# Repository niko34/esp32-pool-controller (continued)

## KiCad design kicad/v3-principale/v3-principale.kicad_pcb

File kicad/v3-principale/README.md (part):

# Carte principale du PCB v3 — composants et connexions

Troisième carte du v3 ([feature-215](../../specs/features/todo/feature-215-conception-du-pcb-v3.md)),
à côté de la carte de mesure ([`../v3-mesure-std/`](../v3-mesure-std/README.md)).
Elle porte l'ESP32, le port USB, l'horloge et sa pile, les sorties de puissance, les
régulateurs et la sonde de température.

⏳ **État au 2026-11-25 : liste des composants et tableau des connexions, version 0.2 —
relus une fois par `electronics-reviewer`, quatre erreurs corrigées (voir « Relecture »).
Schéma rév. 0.2 écrit par script, relu par `electronics-reviewer` : aucune erreur, deux remarques portées.
**Carte rév. 0.1 placée et routée le 2026-11-26** — contrôle des règles : 0 violation, 0 liaison
manquante, 0 écart avec le schéma. Relue par `electronics-reviewer` : aucune erreur, cinq
retouches portées. ⏳ Rien n'est encore ouvert dans KiCad par l'utilisateur.** Horloge : **DS3231SN** depuis le 2026-11-26 (décision de l'utilisateur : la qualité l'emporte sur le nombre de fabricants et sur le prix) ; carte retouchée à la main, contrôle des règles identique.

🆕 **Rév. 0.3 du 2026-11-28 — étude des parasites et de la fiabilité** (demande de l'utilisateur).
Trois changements, détaillés plus bas : une **coupure commune du 12 V des pompes avec relecture de
leurs sorties**, la **protection du bornier de la sonde de température**, et le cuivre mal relié
(piste au bord retirée, plans de masse cousus). Les règles à tenir désormais, avec leurs raisons,
sont dans [`../REGLES-CEM-ET-FIABILITE.md`](../REGLES-CEM-ET-FIABILITE.md) ;
`python3 scripts/verifier_regles_cartes.py v3-principale` les contrôle.
⚠️ **Deux broches de l'ESP32 changent de rôle par rapport au v2** : voir le tableau des connexions.

## Les fichiers de ce dossier

| Fichier | Rôle |
|---|---|
| `generer_schema.py` | écrit le schéma depuis les connexions ci-dessous. ⚠️ Le relancer **réécrit** le schéma en entier. Il lit les symboles standard de KiCad (paquet `kicad-symbols`) |
| `v3-principale.kicad_sch` | le schéma, format A1, un cadre par fonction |
| `v3-principale.kicad_sym`, `sym-lib-table` | le symbole du module ESP32, absent des bibliothèques de KiCad |
| `v3-principale.kicad_pro` | le projet |

**Comment le schéma est fait** : chaque broche porte un bout de fil et une étiquette ; deux
broches sont reliées quand elles portent la même étiquette. Il n'y a pas de long fil à suivre.

**Vérifié le 2026-11-25** : la liste des connexions que KiCad extrait du schéma est identique
à celle voulue — 62 fils, 20 broches en l'air (schéma rév. 0.2).
**Rév. 0.3, vérifié le 2026-11-28** : 63 fils, 23 broches en l'air, 106 pièces ; le schéma du
projet est exactement celui que produit `generer_schema.py` (contrôle C2 du vérificateur).
⚠️ Toute pièce nouvelle s'ajoute dans la **dernière section** du script : il numérote les pièces
dans l'ordre où elles sont écrites.

**Le contrôle électrique de KiCad rend un message attendu** : « deux sorties d'alimentation
reliées », entre la broche V3 du pont USB et la sortie du régulateur 3,3 V. C'est le câblage
que demande le fabricant du pont quand il est alimenté en 3,3 V. Les autres messages
viennent des bibliothèques absentes de la machine qui a généré le schéma.

**Ce que le schéma ne contient pas encore**
- les empreintes du module ESP32 (absente de KiCad, à dessiner d'après la fiche d'Espressif)
  et du support de pile (celle posée est provisoire) ;
- les trous de fixation, qui viendront avec la carte.

Règle suivie : D8 de feature-215 — composants courants, posés par l'atelier, un équivalent
d'un autre fabricant sur la même empreinte, la qualité restant un critère majeur.

## Ce que la carte reprend du v2, et ce qui change

| Fonction | v2 | v3 |
|---|---|---|
| ESP32 | carte de développement enfichée | module soudé, mémoire PSRAM comprise |
| Programmation | par le port de la carte de développement | port USB-C sur la carte |
| Horloge | module externe enfiché (`J11`) | puce et pile sur la carte |
| Sorties 12 V (2 pompes, filtration, éclairage, auxiliaire) | 5 transistors TO-220 traversants | 5 transistors CMS |
| Entrée 12 V : fusible, anti-inversion, écrêteur | traversants | CMS, même principe |
| 3,3 V et 5 V | deux modules enfichés | régulateurs sur la carte — ⚠️ **provisoire, voir plus bas** |
| Température | une sonde sur la carte, une prise pour la sonde d'eau | inchangé |
| Mesure pH et ORP | sur la carte | partie sur la carte de mesure, reliée par câble |

⭐ **Les broches de l'ESP32 ne changent pas** (ADR-0012) : le même firmware pilote les
mêmes sorties sur le v2 et le v3.
⚠️ **Sauf pour doser, depuis la rév. 0.3** : les pompes ne reçoivent le 12 V que si le logiciel
met IO4 à 1 (voir « Sécurité des pompes »). Le firmware du v2, qui ne connaît pas cette broche,
pilote tout le reste mais ne fait tourner aucune pompe sur cette carte.

## Disposition dans le boîtier — décidée le 2026-11-25 (utilisateur)

Relevé sur le fichier d'assemblage FreeCAD du boîtier V14 (reçu le 2026-11-25, conservé hors
du dépôt). Origine : coin bas-gauche du boîtier vu de face, cotes en mm.

| Élément | Position relevée |
|---|---|
| Boîtier | 210 × 175, profondeur 94 (119,5 avec les pompes) |
| Alimentation RPS-30-12 | X 18,8 à 69,6 · Y 39,9 à 116,1 ; son capot va jusqu'à X = 75,6 et monte à 40 mm du fond |
| Carte v2 | X 76,6 à 196 · Y 13,5 à 132,9, dos à 12 mm du fond |
| Pompes doseuses (sur le capot avant) | moteurs Ø 25,5 centrés en (65 ; 91) et (145 ; 91), profonds de 44,9 mm : leur arrière est à 43 mm du fond, soit 10,5 mm au-dessus des composants |
| Entrées de câbles (paroi du bas) | trois, à X = 44 / 68 / 88, à **49 mm du fond** : les câbles arrivent au-dessus du capot de l'alimentation |
| Prises des sondes (paroi du bas) | X = 123,1 et 159,4, à 19,8 mm du fond |
| Plots de fixation murale | (25 ; 150) et (185 ; 150) : ils bornent la carte en haut |

**Organisation retenue (« option N »)** — le dessin général du boîtier ne change pas, il
gagne **20 mm en hauteur** (210 × 195) **et 10 mm en profondeur** (104 mm, 129,5 mm avec les
pompes) :

⚠️ **Profondeur portée à 114 mm le 2026-11-26** (139,5 mm avec les pompes), pour qu'un
transformateur de 48 mm tienne sous la pompe de gauche (feature-218). Le boîtier adapté est
`boitier/v15/` : ses cotes font foi.

- alimentation à gauche, pompes à leur place actuelle ;
- carte de mesure en bas à droite, prises des sondes sur les perçages existants ;
- **carte principale rectangulaire de 119 × 100 mm** au-dessus : X 77 à 196, Y 62 à 162 ;
- le connecteur de liaison est sur le bord du bas de la carte principale, **face à celui de
  la carte de mesure** ;
- **tout se branche par le dessus**, sur des borniers débrochables ;
- **tous les câbles du boîtier sont sur le bord gauche, en une seule colonne** (utilisateur,
  2026-11-26), de haut en bas : arrivée 12 V — en haut à gauche, pour la relier par le haut à
  l'alimentation —, filtration, éclairage, auxiliaire, sonde d'eau, détecteur de débit ;
- les deux pompes, dont les fils viennent du capot, sont sur le bord du haut ;
- le 5 V d'essai est à l'intérieur de la carte : aucun câble du boîtier n'y arrive ;
- ⛔ aucun connecteur haut sous le moteur de la pompe de droite : centre en (68 ; 71) sur la
  carte, Ø 25,5, 29 mm de libre au-dessus de la carte ;
- antenne de l'ESP32 dans le coin haut-droit.

**Connecteurs — décidé le 2026-11-25 (utilisateur) : uniquement des borniers débrochables**
pour tout ce qui reçoit des fils. On visse les fils sur une fiche, puis on l'enfiche par le
dessus : aucune place n'est nécessaire sur le côté.

| Connexion | Bornier |
|---|---|
| Arrivée 12 V, filtration, éclairage, auxiliaire, 5 V d'essai | 5,08 mm, 2 broches |
| Sonde de température de l'eau | 5,08 mm, 3 broches |
| Pompe pH, pompe chlore, détecteur de débit | 3,81 mm, 2 broches |

Restent d'un autre type : la liaison vers la carte de mesure (JST XH 8 voies, câble tout
fait), la prise USB-C et l'embase de débogage.

**Repérage par la couleur** (utilisateur, 2026-11-25) : les prises de même format sont
distinguées par une pastille ou un cerclage de couleur, sur la carte et sur la fiche.
L'idée de borniers à broches vides pour empêcher les erreurs a été écartée : fonctionnelle,
mais pas élégante.
⚠️ Risque assumé, à couvrir par les couleurs : le pas de 3,81 mm sépare les pompes des
sorties de filtration et d'éclairage, mais rien n'empêche mécaniquement d'inverser les deux
pompes, ni d'enficher le détecteur de débit sur une sortie de pompe (court-circuit du 12 V
à travers le transistor dès que la pompe est commandée). ⏳ À faire à la carte : sérigraphie
de couleur ou repère net à côté de chaque prise.

**Pourquoi 10 mm de profondeur en plus** (utilisateur, 2026-11-25) — jeux mesurés sur le
fichier d'assemblage, moteur de 44,9 mm de profondeur (cote « nominale », ⏳ à mesurer sur
une pompe réelle, cosses comprises) :

| Entre | Aujourd'hui | Avec 10 mm de plus |
|---|---|---|
| moteur de la pompe de gauche et capot de l'alimentation | 3,1 mm | 13,1 mm |
| moteur de la pompe de gauche et l'alimentation | 10,1 mm | 20,1 mm |
| moteur de la pompe de droite et la carte principale | 29,7 mm | 39,7 mm |

Le moteur de gauche empiétait aussi sur la zone réservée aux câbles devant la carte.

⏳ À faire avec le boîtier : déplacer les deux plots de fixation du haut, vérifier la
hauteur d'un bornier débrochable avec sa fiche (environ 20 mm), relever la référence des
fiches à vis (une par câble, à fournir avec l'appareil).

## La carte (2026-11-26)

119 × 100 mm, quatre couches, quatre trous M3. ⚠️ **Le coin haut-droit est découpé** sous
l'antenne du module ESP32 (x 97,5 à 119, y 0 à 6) : l'antenne dépasse dans le vide, comme le
demande Espressif. `generer_carte.py` pose encore un contour rectangulaire ; c'est la
retouche 6 qui le découpe. Couches : composants et signaux dessus, masse
continue en couche 2, 3,3 V en couche 3, signaux et masse dessous. Des plans de masse
entourent les pistes sur les deux faces extérieures.

| Fichier | Rôle |
|---|---|
| `generer_carte.py` | pose les composants, les trous et les deux plans internes. ⚠️ Le relancer **réécrit** la carte et **efface le routage** |
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
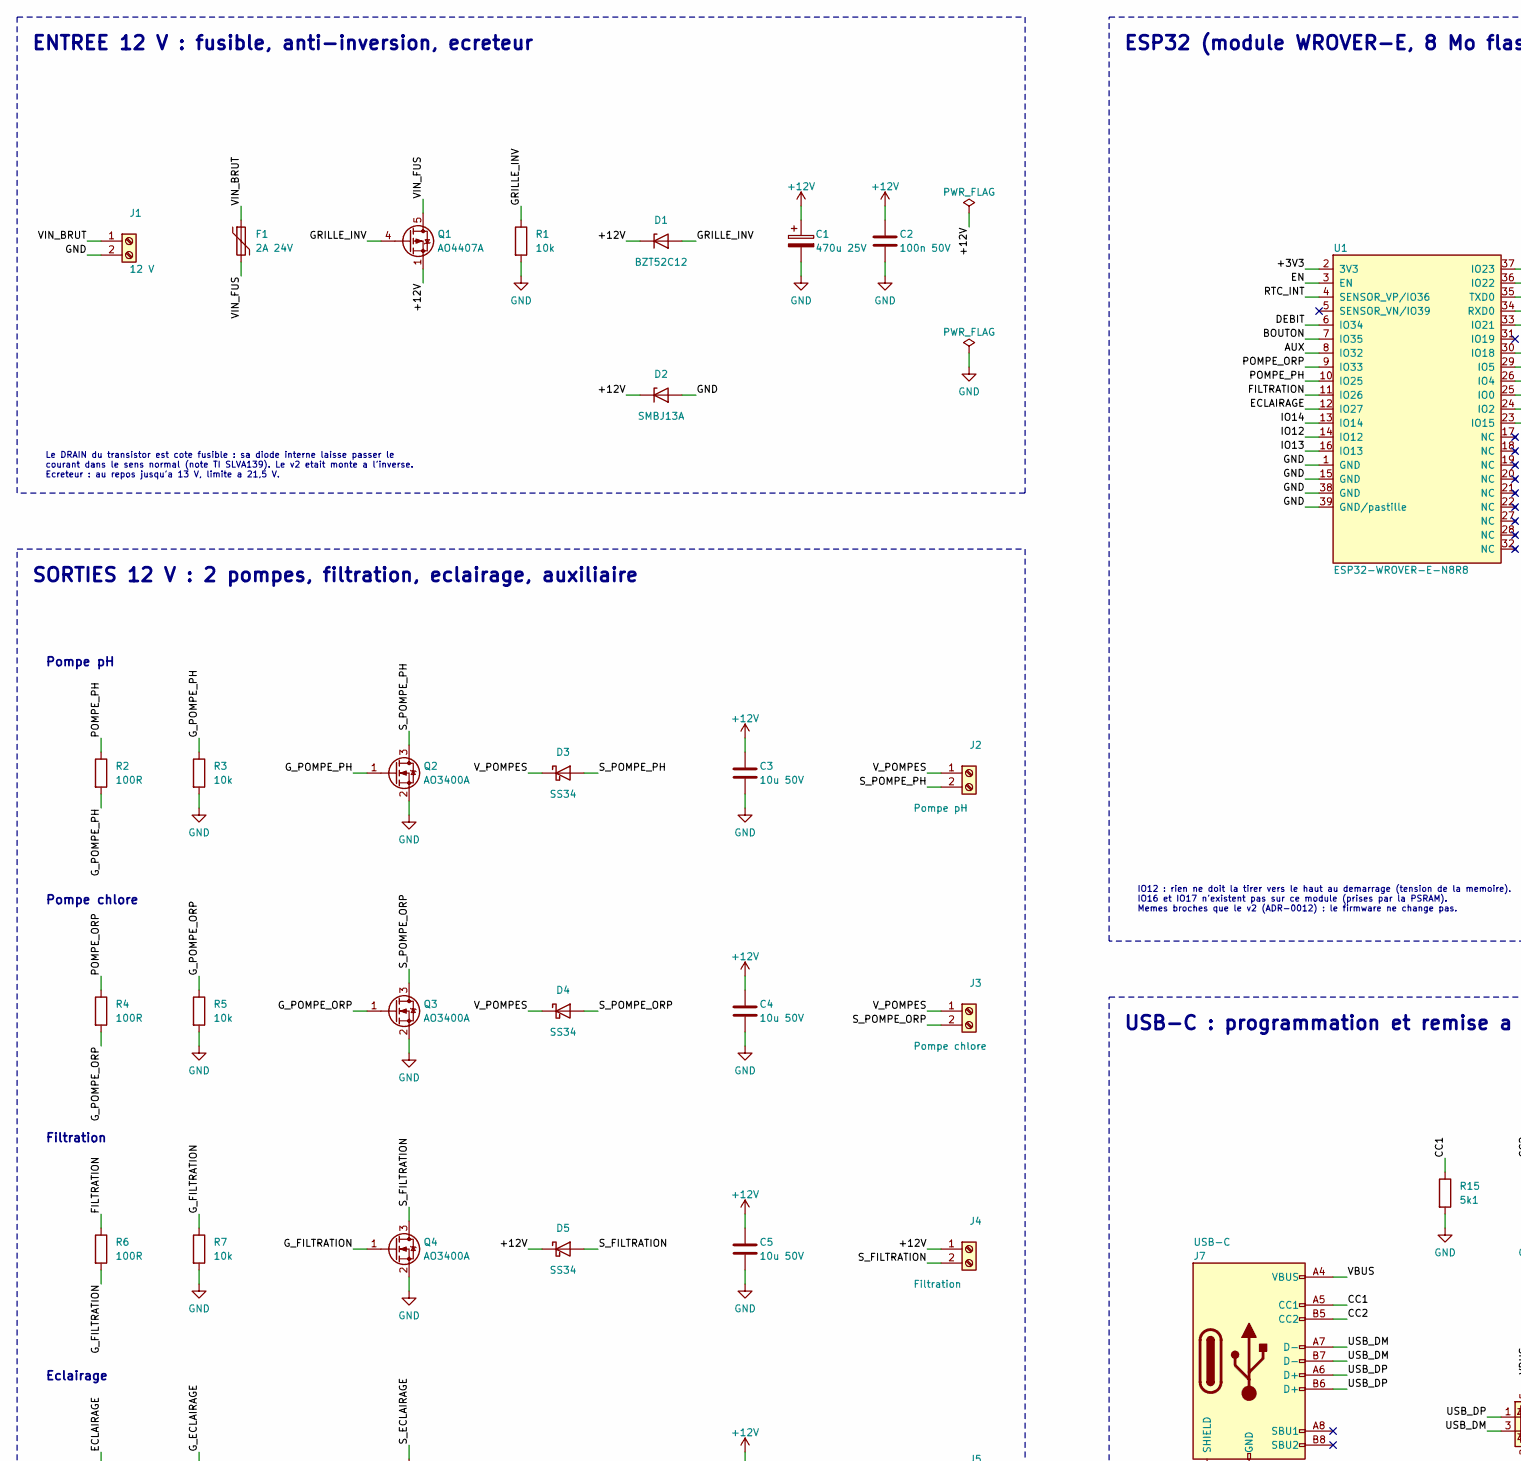
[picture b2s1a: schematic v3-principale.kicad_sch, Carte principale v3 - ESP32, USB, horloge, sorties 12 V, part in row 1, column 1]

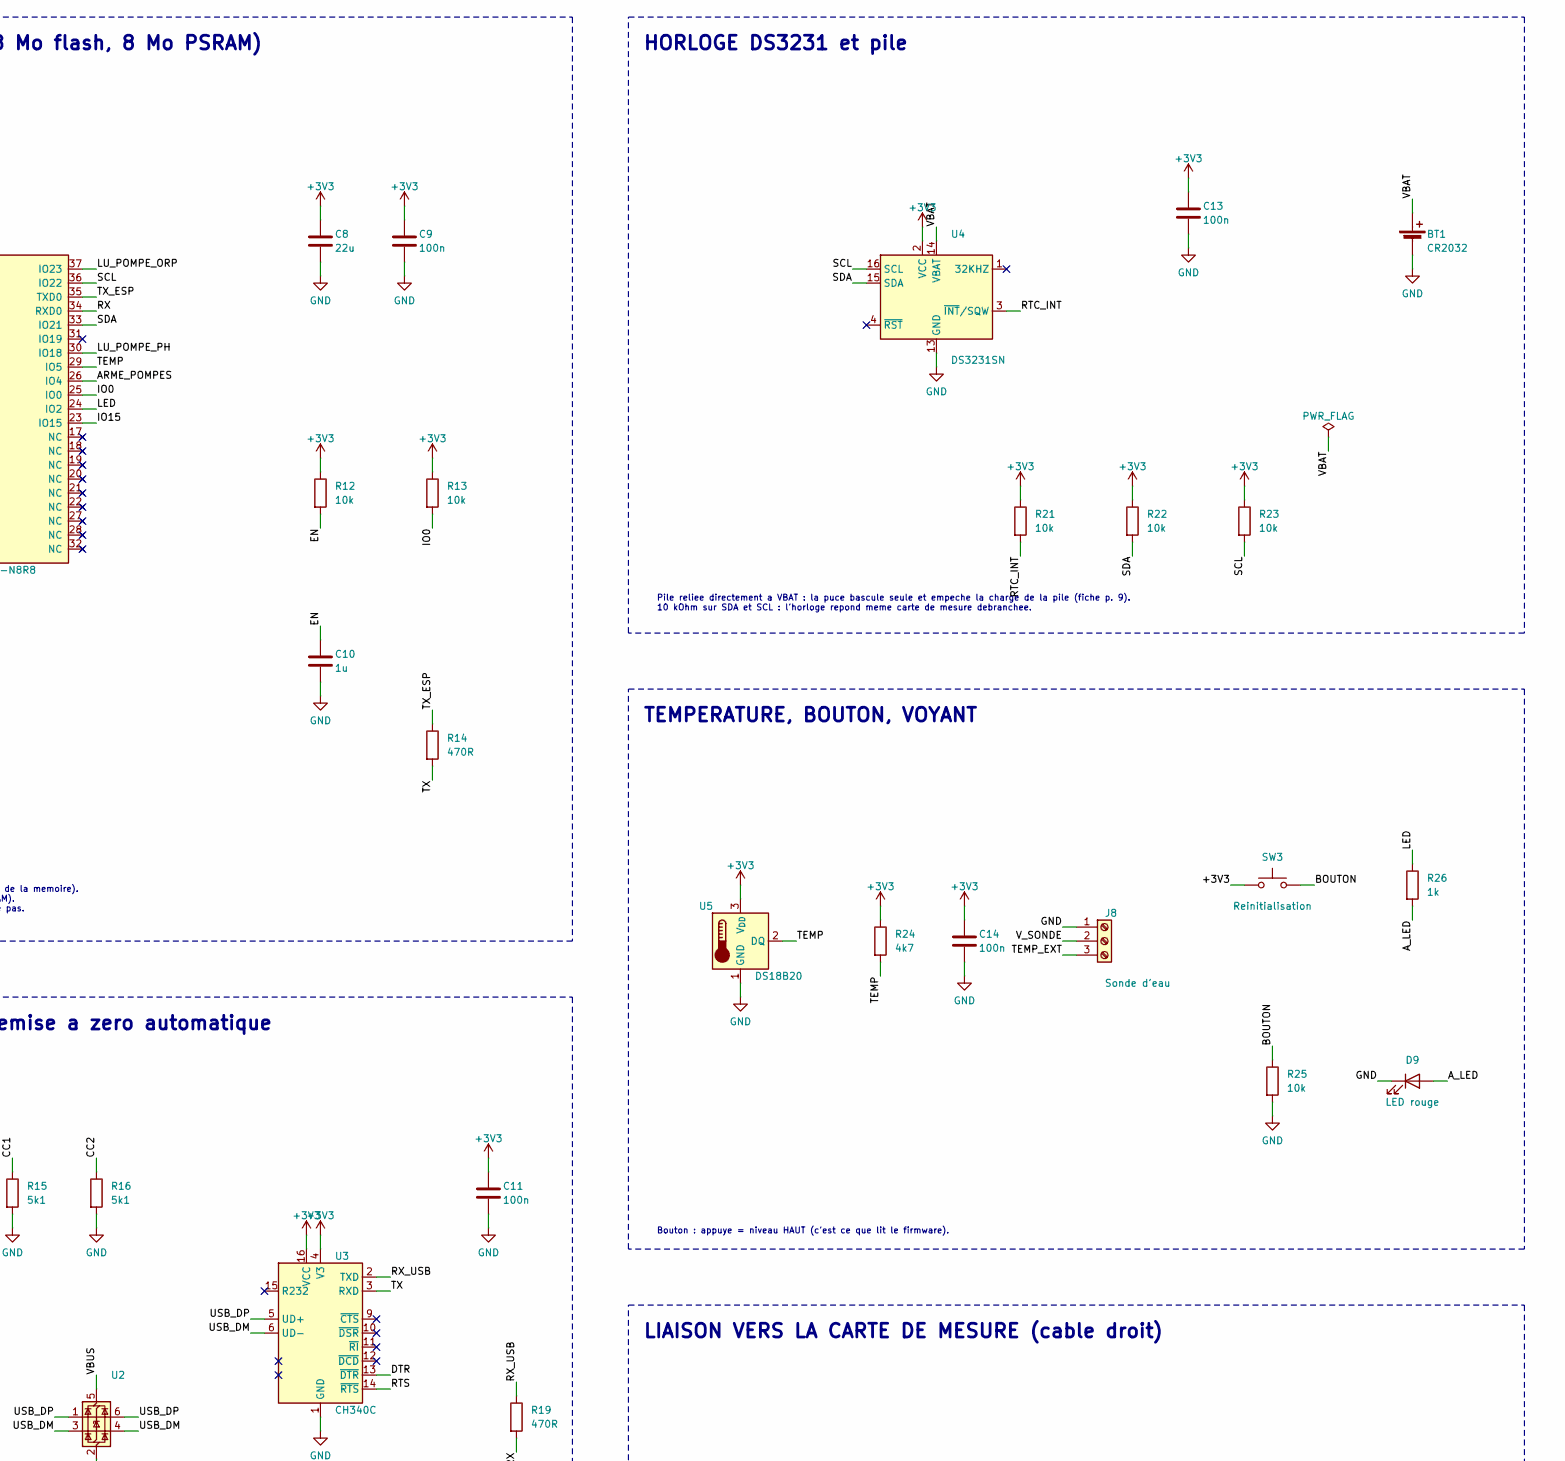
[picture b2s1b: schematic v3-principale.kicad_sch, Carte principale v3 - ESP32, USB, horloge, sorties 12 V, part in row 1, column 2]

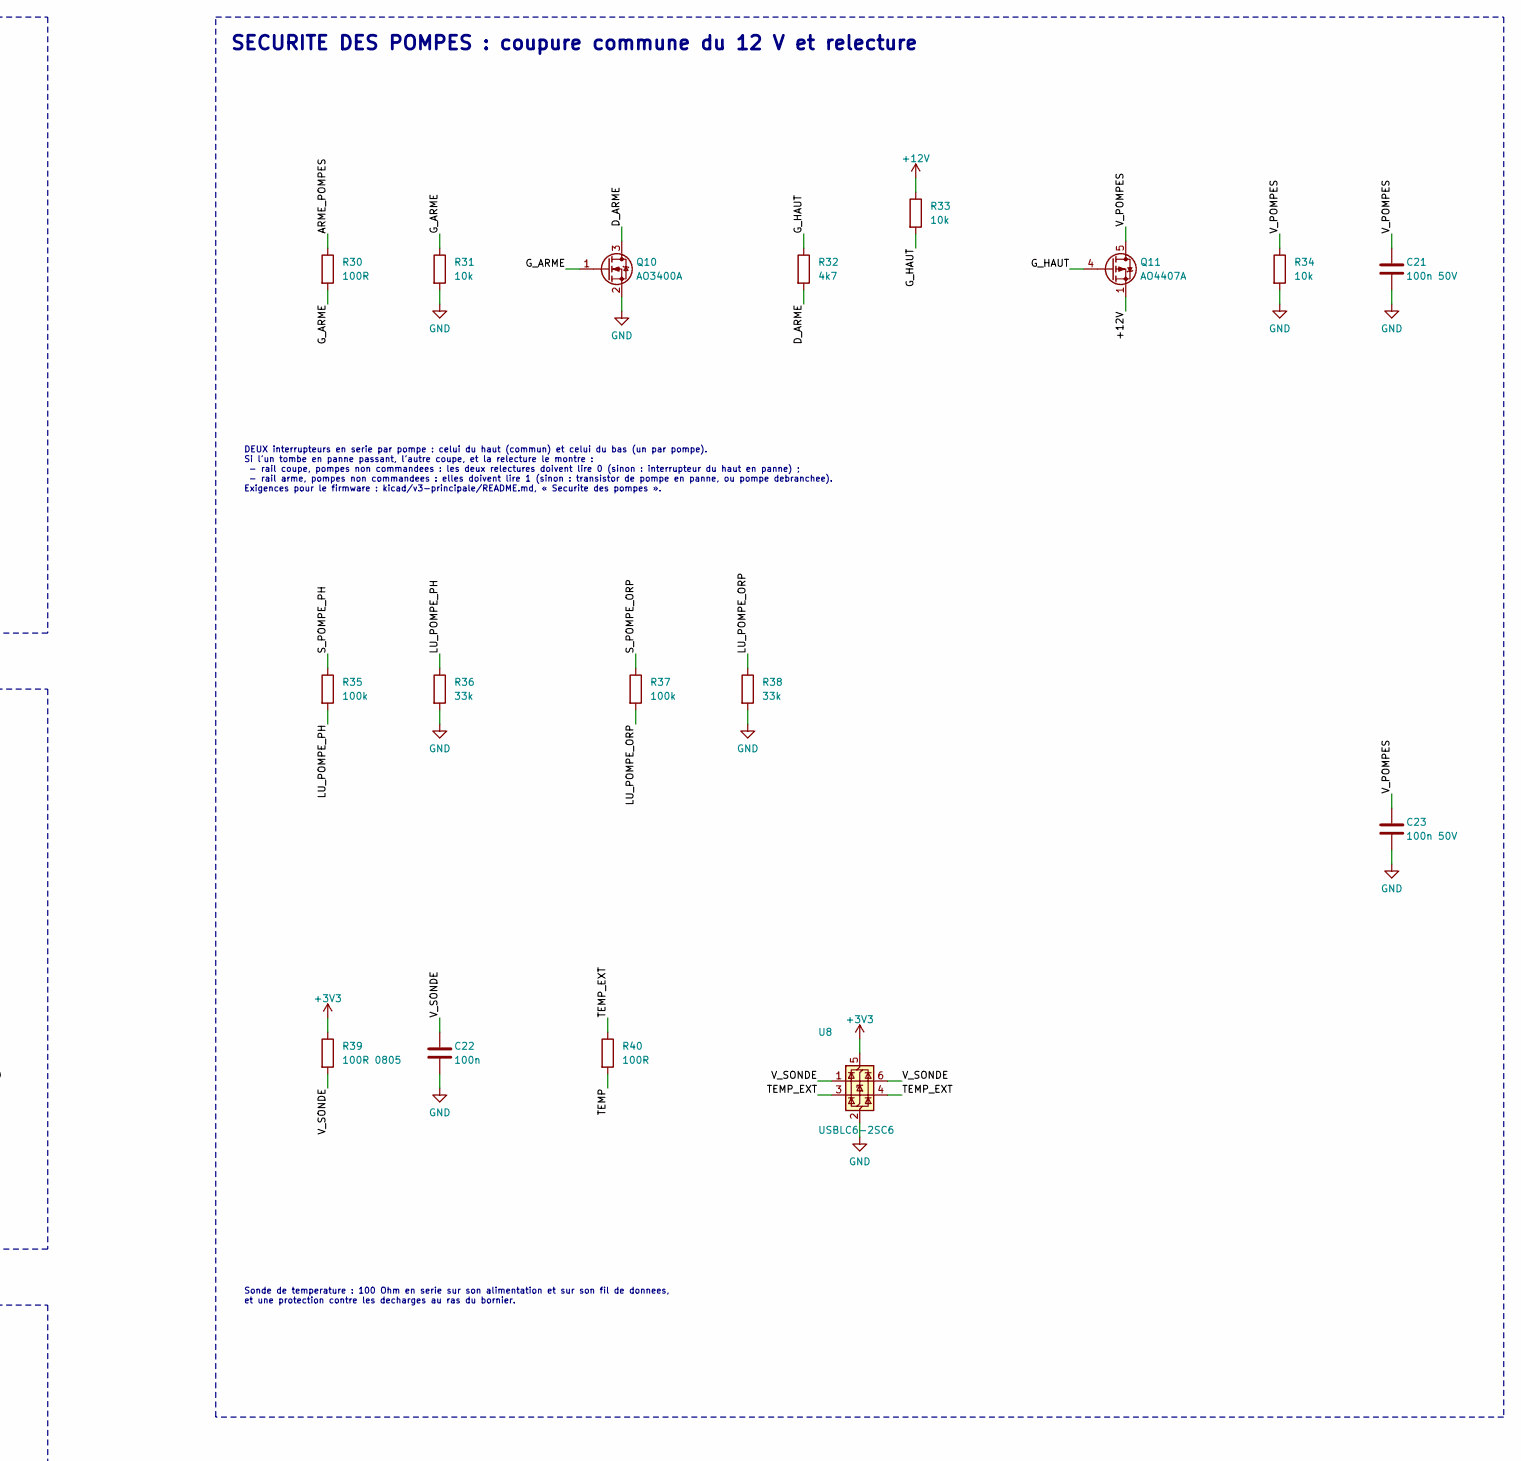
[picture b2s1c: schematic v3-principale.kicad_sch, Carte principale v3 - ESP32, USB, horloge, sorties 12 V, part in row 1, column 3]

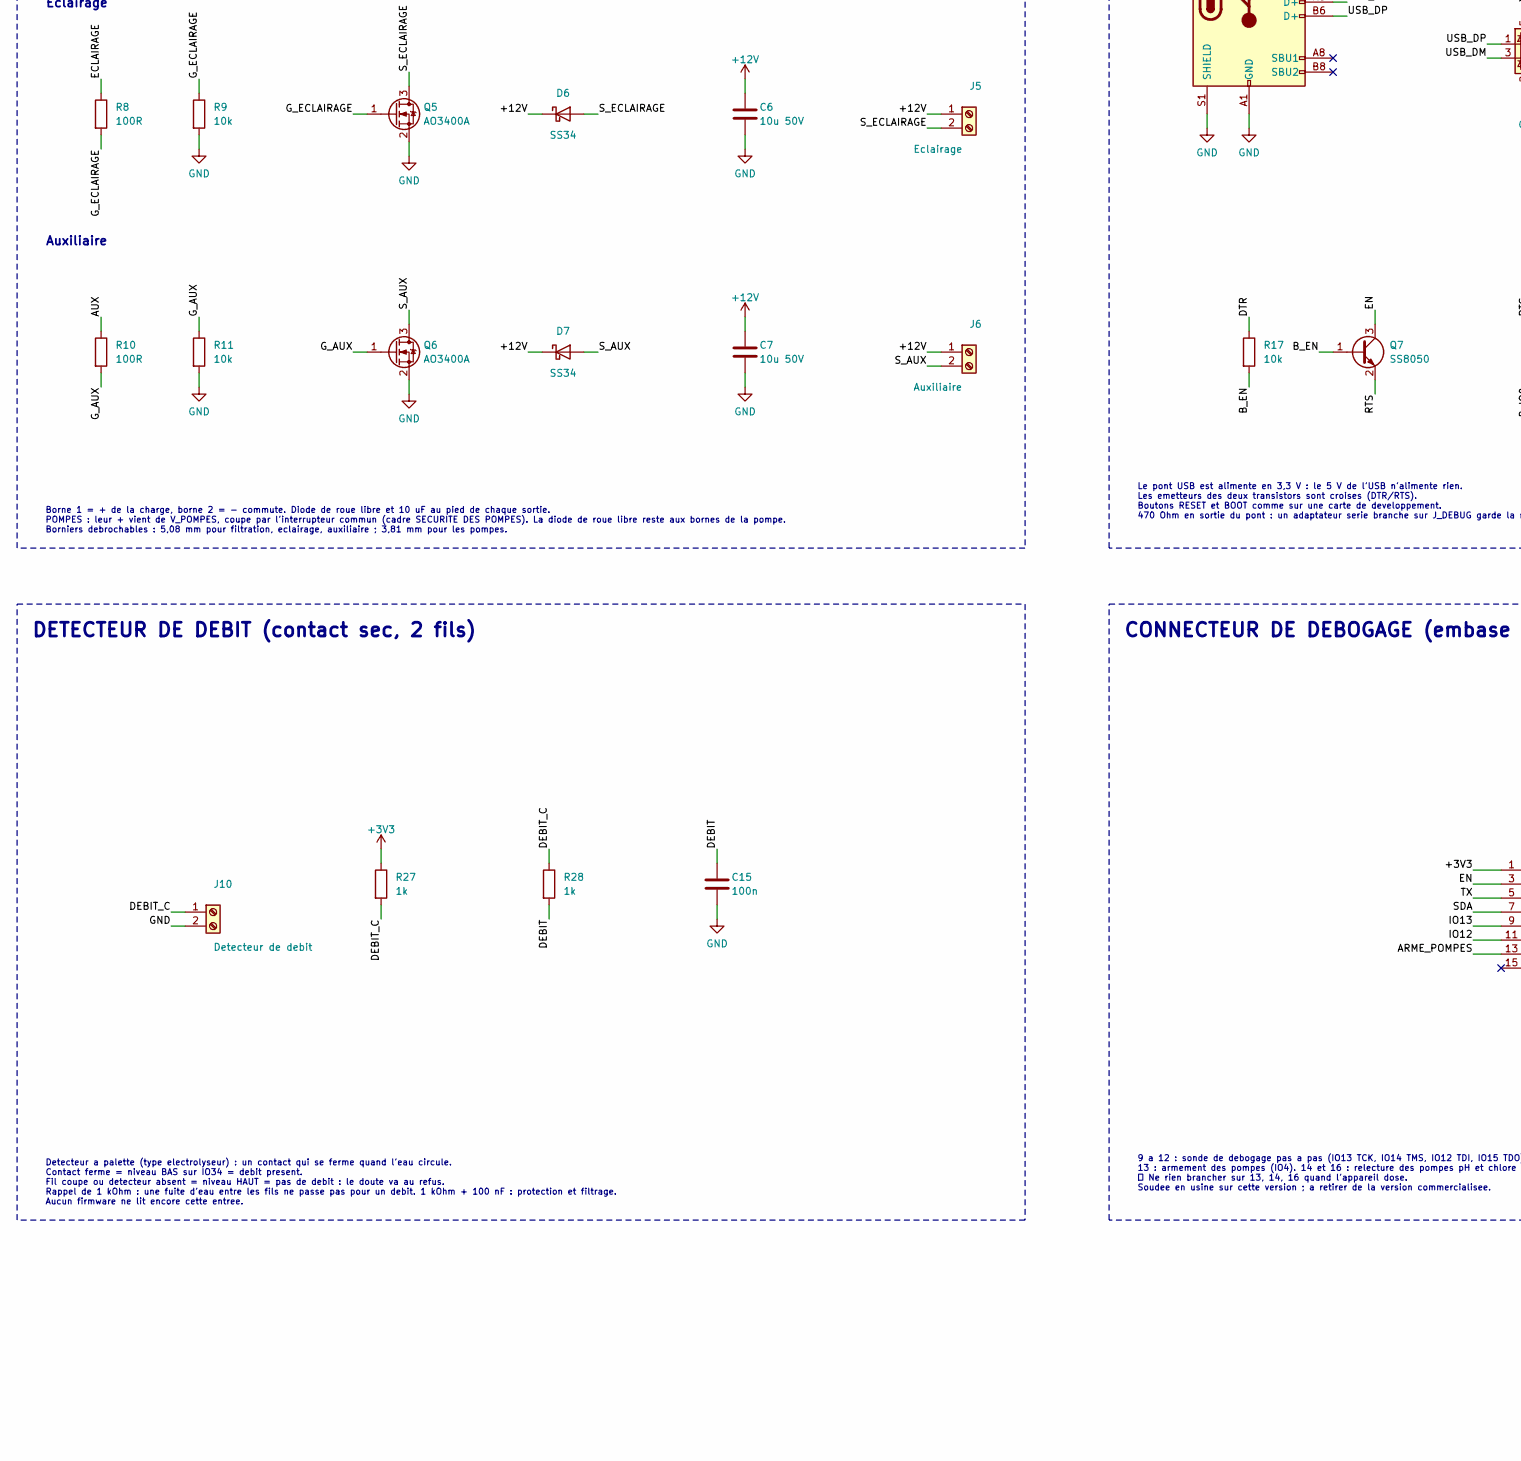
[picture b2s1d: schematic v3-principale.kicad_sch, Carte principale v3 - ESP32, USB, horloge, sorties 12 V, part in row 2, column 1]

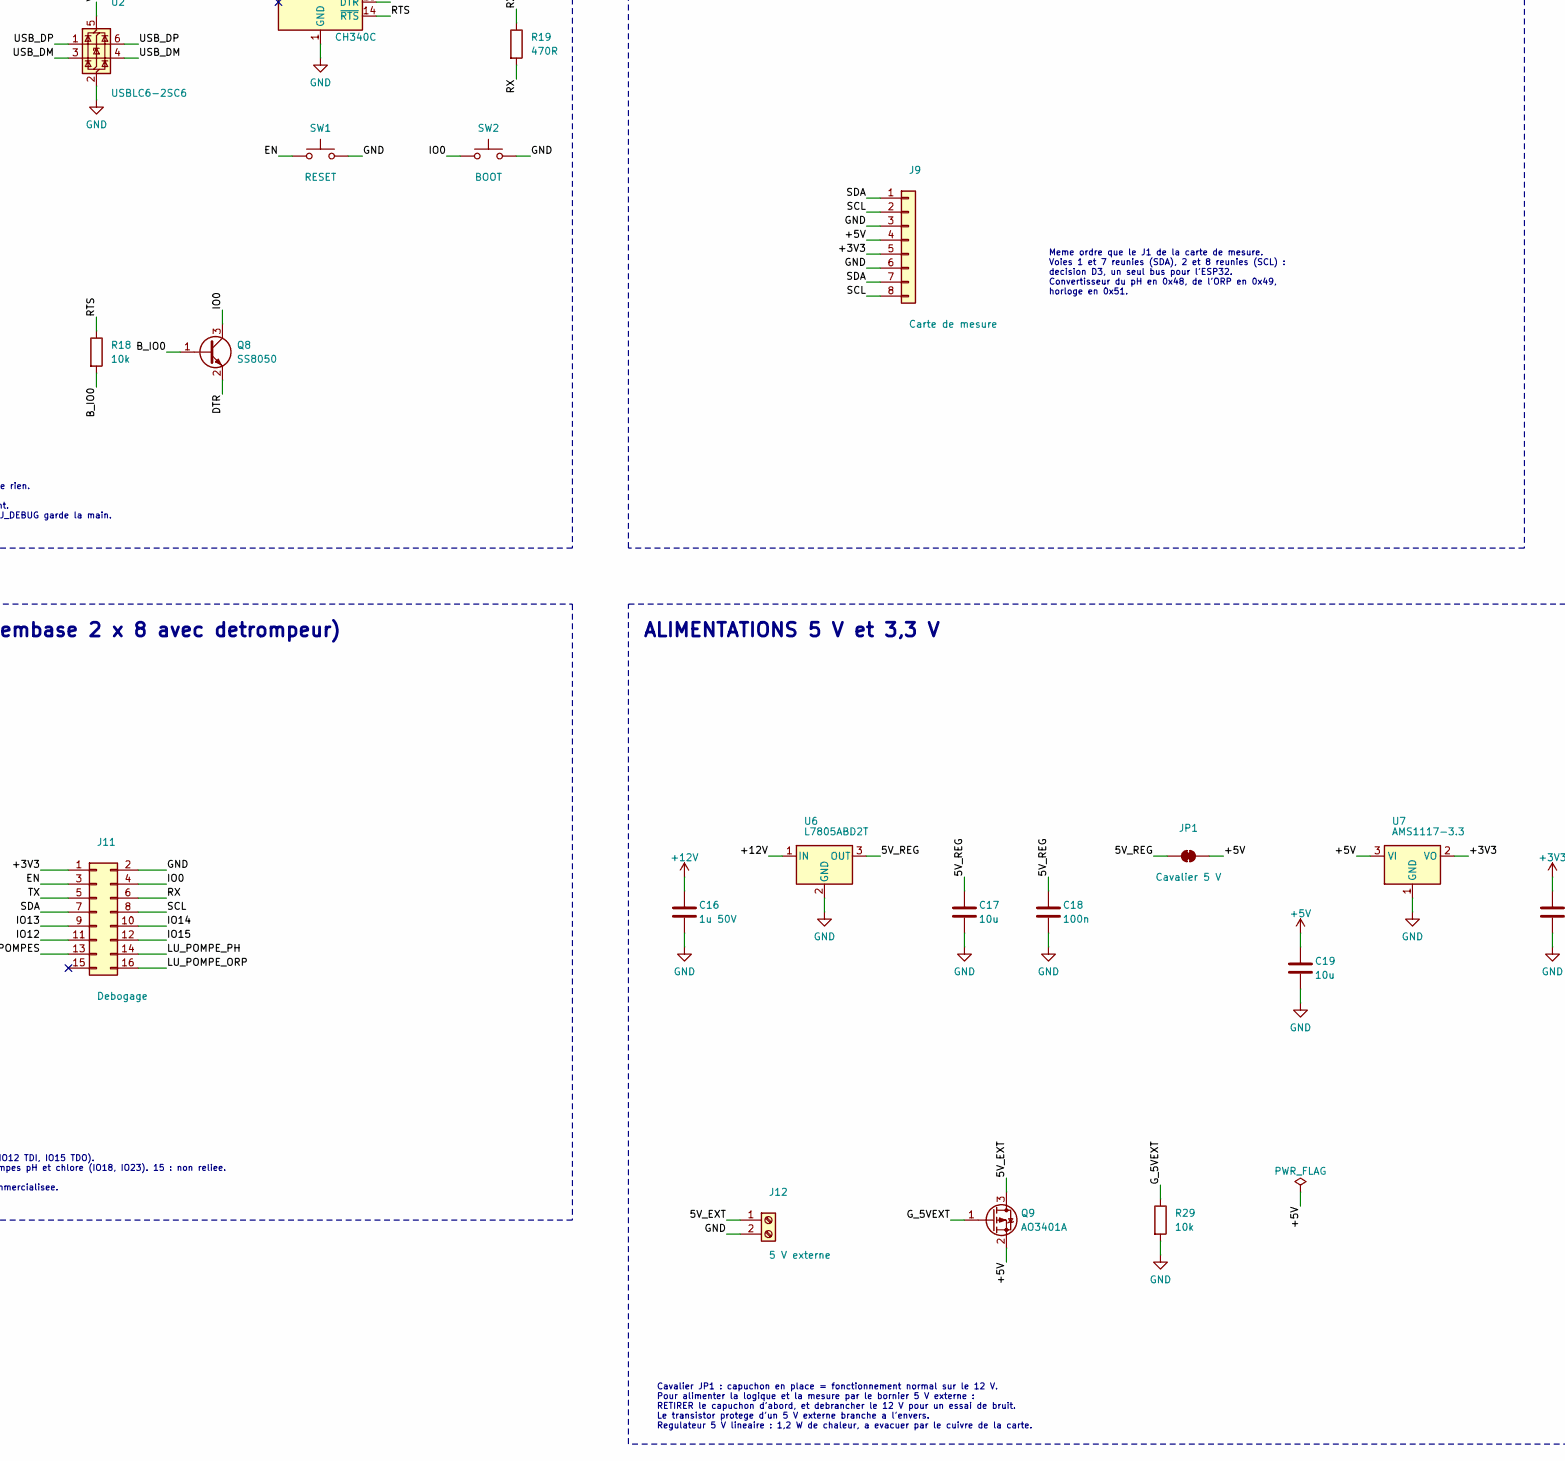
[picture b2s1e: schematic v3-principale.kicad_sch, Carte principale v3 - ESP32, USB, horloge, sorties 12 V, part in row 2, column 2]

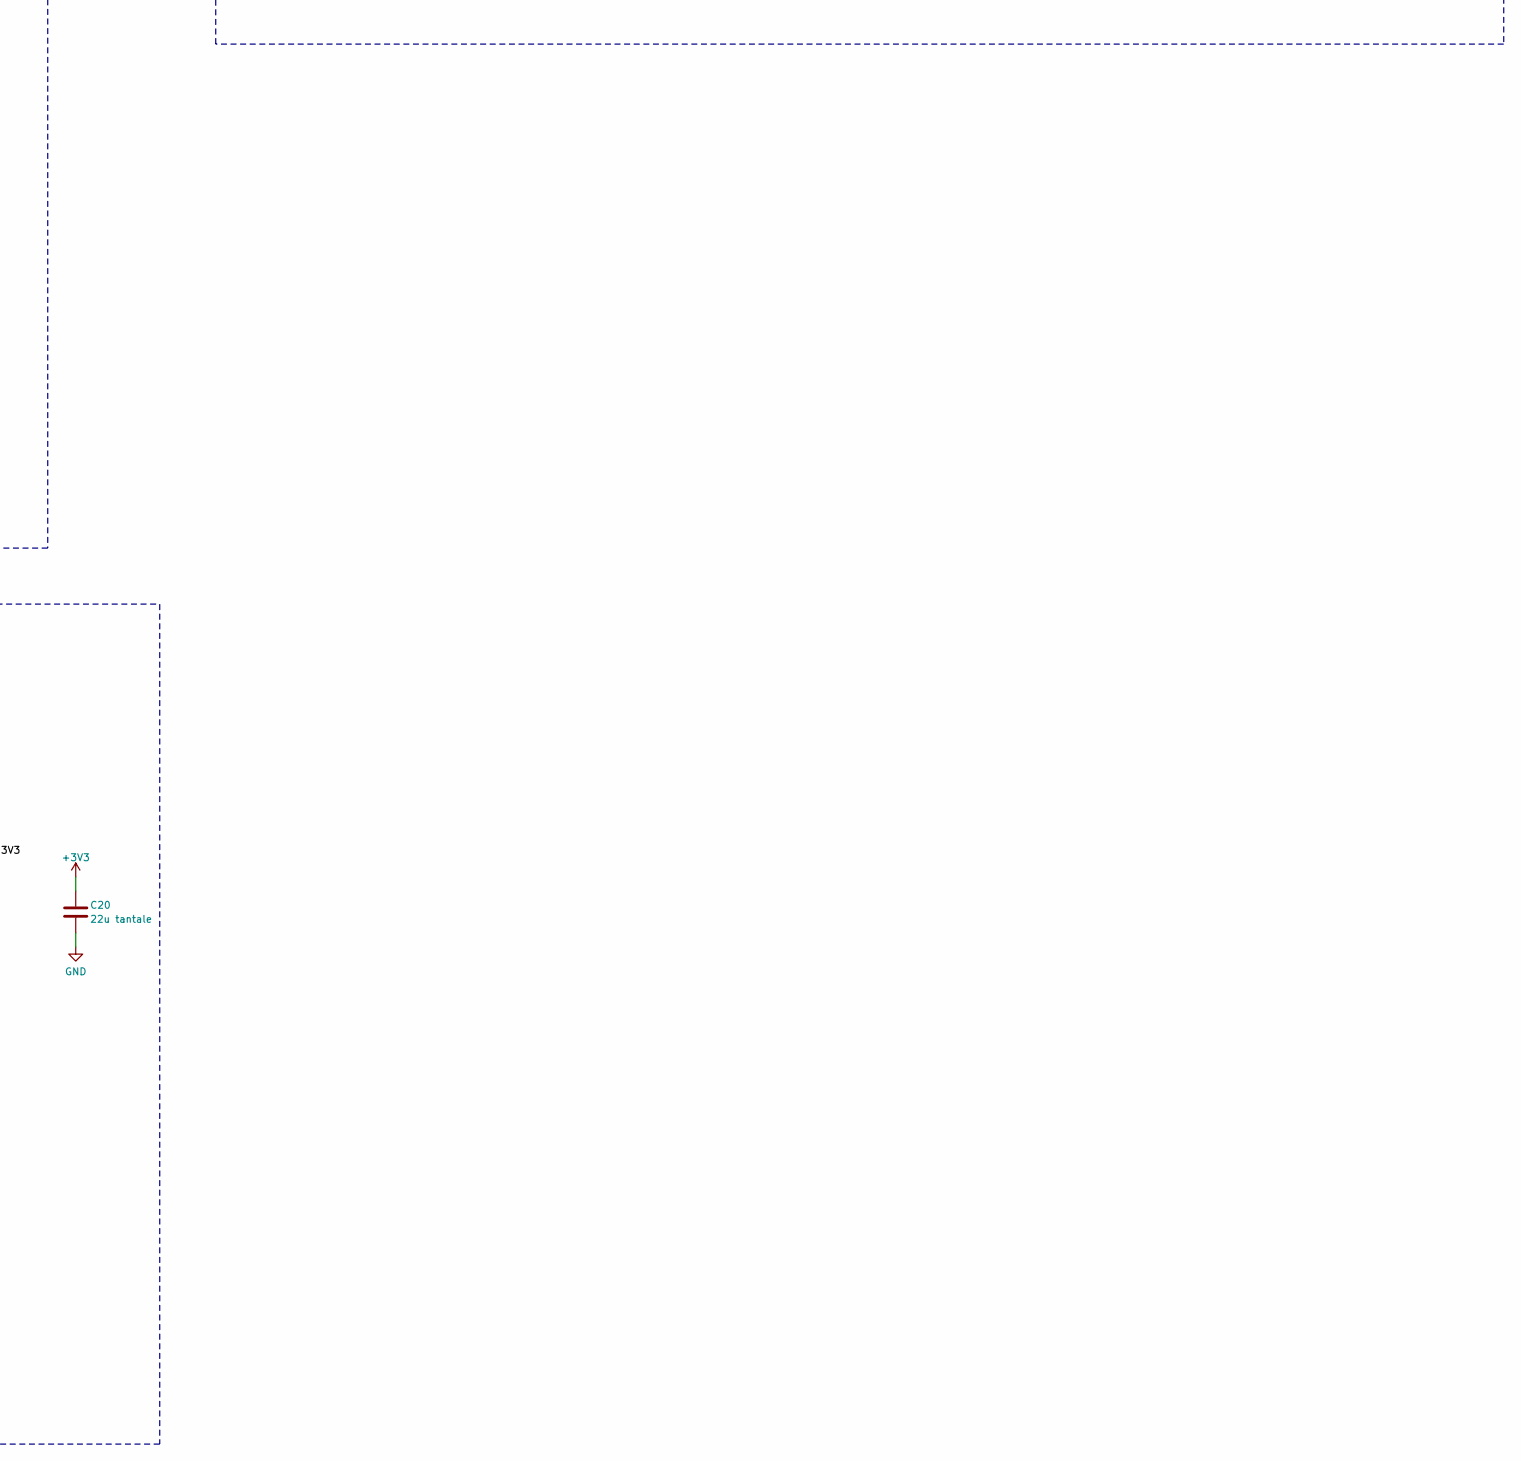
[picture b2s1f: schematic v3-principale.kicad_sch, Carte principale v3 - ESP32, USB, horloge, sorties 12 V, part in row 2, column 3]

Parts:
BT1: CR2032; BatteryHolder_MYOUNG_BS-07-A1BJ001_CR2032; LCSC C2979167
C1: 470u 25V; CP_Radial_D8.0mm_P3.50mm; LCSC C5213783
C2, C21, C23: 100n 50V; C_0402_1005Metric; LCSC C307331
C3, C4, C5, C6, C7: 10u 50V; C_1206_3216Metric; LCSC C13585
C8: 22u; C_0805_2012Metric; LCSC C45783
C9, C11, C13, C14, C15, C18, C22: 100n; C_0402_1005Metric; LCSC C1525
C10: 1u; C_0603_1608Metric; LCSC C15849
C16: 1u 50V; C_0805_2012Metric; LCSC C28323
C17, C19: 10u; C_0805_2012Metric; LCSC C15850
C20: 22u tantale; CP_EIA-3528-21_Kemet-B; LCSC C8020
D1: BZT52C12; D_SOD-123; LCSC C173429
D2: SMBJ13A; D_SMB; LCSC C404130
D3, D4, D5, D6, D7: SS34; D_SMA; LCSC C8678
D9: LED rouge; LED_0603_1608Metric; LCSC C2286
F1: 2A 24V; Fuse_1812_4532Metric; LCSC C434887
J1: 12 V; PhoenixContact_MSTBVA_2,5_2-G-5,08_1x02_P5.08mm_Vertical; LCSC C505788
J2: Pompe pH; PhoenixContact_MCV_1,5_2-G-3.81_1x02_P3.81mm_Vertical; LCSC C8396
J3: Pompe chlore; PhoenixContact_MCV_1,5_2-G-3.81_1x02_P3.81mm_Vertical; LCSC C8396
J4: Filtration; PhoenixContact_MSTBVA_2,5_2-G-5,08_1x02_P5.08mm_Vertical; LCSC C505788
J5: Eclairage; PhoenixContact_MSTBVA_2,5_2-G-5,08_1x02_P5.08mm_Vertical; LCSC C505788
J6: Auxiliaire; PhoenixContact_MSTBVA_2,5_2-G-5,08_1x02_P5.08mm_Vertical; LCSC C505788
J7: USB-C; USB_C_Receptacle_HRO_TYPE-C-31-M-12; LCSC C165948
J8: Sonde d'eau; PhoenixContact_MSTBVA_2,5_3-G-5,08_1x03_P5.08mm_Vertical; LCSC C505789
J9: Carte de mesure; JST_XH_B8B-XH-A_1x08_P2.50mm_Vertical; LCSC C157972
J10: Detecteur de debit; PhoenixContact_MCV_1,5_2-G-3.81_1x02_P3.81mm_Vertical; LCSC C8396
J11: Debogage; IDC-Header_2x08_P2.54mm_Vertical; LCSC C221049
J12: 5 V externe; PhoenixContact_MSTBVA_2,5_2-G-5,08_1x02_P5.08mm_Vertical; LCSC C505788
JP1: Cavalier 5 V; PinHeader_1x02_P2.54mm_Vertical; LCSC C124375
Q1, Q11: AO4407A; SOIC-8_3.9x4.9mm_P1.27mm; LCSC C16072
Q2, Q3, Q4, Q5, Q6, Q10: AO3400A; SOT-23; LCSC C20917
Q7, Q8: SS8050; SOT-23; LCSC C2150
Q9: AO3401A; SOT-23; LCSC C15127
R1, R3, R5, R7, R9, R11, R12, R13, R17, R18, R21, R22, R23, R25, R29, R31, R33, R34: 10k; R_0603_1608Metric; LCSC C25804
R2, R4, R6, R8, R10, R30, R40: 100R; R_0603_1608Metric; LCSC C22775
R14, R19: 470R; R_0603_1608Metric; LCSC C23179
R15, R16: 5k1; R_0603_1608Metric; LCSC C23186
R24, R32: 4k7; R_0603_1608Metric; LCSC C23162
R26, R27, R28: 1k; R_0603_1608Metric; LCSC C21190
R35, R37: 100k; R_0603_1608Metric; LCSC C25803
R36, R38: 33k; R_0603_1608Metric; LCSC C4216
R39: 100R 0805; R_0805_2012Metric; LCSC C17408
SW1: RESET; SW_Push_1P1T_XKB_TS-1187A; LCSC C318884
SW2: BOOT; SW_Push_1P1T_XKB_TS-1187A; LCSC C318884
SW3: Reinitialisation; SW_Push_1P1T_XKB_TS-1187A; LCSC C318884
U1: ESP32-WROVER-E-N8R8; ESP32-WROVER-E; LCSC C2973667
U2, U8: USBLC6-2SC6; SOT-23-6; LCSC C7519
U3: CH340C; SOIC-16_3.9x9.9mm_P1.27mm; LCSC C84681
U4: DS3231SN; SOIC-16W_7.5x10.3mm_P1.27mm; LCSC C9866
U5: DS18B20; TO-92_Inline; LCSC C9753
U6: L7805ABD2T; TO-263-2; LCSC C86206
U7: AMS1117-3.3; SOT-223-3_TabPin2; LCSC C6186

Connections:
+3V3: C8.1, C9.1, C11.1, C13.1, C14.1, C20.1, J9.5, J11.1, R12.1, R13.1, R21.1, R22.1, R23.1, R24.1, R27.1, R39.1, SW3.1, U1.2 (3V3), U3.4 (V3), U3.16 (VCC), U4.2 (VCC), U5.3 (V_{DD}), U7.2 (VO), U8.5 (VBUS)
+5V: C19.1, J9.4, JP1.2 (B), Q9.2 (S), U7.3 (VI)
+12V: C1.1, C2.1, C3.1, C4.1, C5.1, C6.1, C7.1, C16.1, D1.1 (K), D2.1 (K), D5.1 (K), D6.1 (K), D7.1 (K), J4.1, J5.1, J6.1, Q1.1 (S), Q1.2 (S), Q1.3 (S), Q11.1 (S), Q11.2 (S), Q11.3 (S), R33.1, U6.1 (IN)
/5V_EXT: J12.1, Q9.3 (D)
/5V_REG: C17.1, C18.1, JP1.1 (A), U6.3 (OUT)
/ARME_POMPES: J11.13, R30.1, U1.26 (IO4)
/AUX: R10.1, U1.8 (IO32)
/A_LED: D9.2 (A), R26.2
/BOUTON: R25.1, SW3.2, U1.7 (IO35)
/B_EN: Q7.1 (B), R17.2
/B_IO0: Q8.1 (B), R18.2
/CC1: J7.A5 (CC1), R15.1
/CC2: J7.B5 (CC2), R16.1
/DEBIT: C15.1, R28.2, U1.6 (IO34)
/DEBIT_C: J10.1, R27.2, R28.1
/DTR: Q8.2 (E), R17.1, U3.13 (~DTR)
/D_ARME: Q10.3 (D), R32.2
/ECLAIRAGE: R8.1, U1.12 (IO27)
/EN: C10.1, J11.3, Q7.3 (C), R12.2, SW1.1, U1.3 (EN)
/FILTRATION: R6.1, U1.11 (IO26)
/GRILLE_INV: D1.2 (A), Q1.4 (G), R1.1
/G_5VEXT: Q9.1 (G), R29.1
/G_ARME: Q10.1 (G), R30.2, R31.1
/G_AUX: Q6.1 (G), R10.2, R11.1
/G_ECLAIRAGE: Q5.1 (G), R8.2, R9.1
/G_FILTRATION: Q4.1 (G), R6.2, R7.1
/G_HAUT: Q11.4 (G), R32.1, R33.2
/G_POMPE_ORP: Q3.1 (G), R4.2, R5.1
/G_POMPE_PH: Q2.1 (G), R2.2, R3.1
/IO0: J11.4, Q8.3 (C), R13.2, SW2.1, U1.25 (IO0)
/IO12: J11.11, U1.14 (IO12)
/IO13: J11.9, U1.16 (IO13)
/IO14: J11.10, U1.13 (IO14)
/IO15: J11.12, U1.23 (IO15)
/LED: R26.1, U1.24 (IO2)
/LU_POMPE_ORP: J11.16, R37.2, R38.1, U1.37 (IO23)
/LU_POMPE_PH: J11.14, R35.2, R36.1, U1.30 (IO18)
/POMPE_ORP: R4.1, U1.9 (IO33)
/POMPE_PH: R2.1, U1.10 (IO25)
/RTC_INT: R21.2, U1.4 (SENSOR_VP/IO36), U4.3 (~INT/SQW)
/RTS: Q7.2 (E), R18.1, U3.14 (~RTS)
/RX: J11.6, R19.2, U1.34 (RXD0)
/RX_USB: R19.1, U3.2 (TXD)
/SCL: J9.2, J9.8, J11.8, R23.2, U1.36 (IO22), U4.16 (SCL)
/SDA: J9.1, J9.7, J11.7, R22.2, U1.33 (IO21), U4.15 (SDA)
/S_AUX: D7.2 (A), J6.2, Q6.3 (D)
/S_ECLAIRAGE: D6.2 (A), J5.2, Q5.3 (D)
/S_FILTRATION: D5.2 (A), J4.2, Q4.3 (D)
/S_POMPE_ORP: D4.2 (A), J3.2, Q3.3 (D), R37.1
/S_POMPE_PH: D3.2 (A), J2.2, Q2.3 (D), R35.1
/TEMP: R24.2, R40.2, U1.29 (IO5), U5.2 (DQ)
/TEMP_EXT: J8.3, R40.1, U8.3 (I/O2), U8.4 (I/O2)
/TX: J11.5, R14.2, U3.3 (RXD)
/TX_ESP: R14.1, U1.35 (TXD0)
/USB_DM: J7.A7 (D-), J7.B7 (D-), U2.3 (I/O2), U2.4 (I/O2), U3.6 (UD-)
/USB_DP: J7.A6 (D+), J7.B6 (D+), U2.1 (I/O1), U2.6 (I/O1), U3.5 (UD+)
/VBAT: BT1.1 (+), U4.14 (VBAT)
/VBUS: J7.A4 (VBUS), J7.A9 (VBUS), J7.B4 (VBUS), J7.B9 (VBUS), U2.5 (VBUS)
/VIN_BRUT: F1.1, J1.1
/VIN_FUS: F1.2, Q1.5 (D), Q1.6 (D), Q1.7 (D), Q1.8 (D)
/V_POMPES: C21.1, C23.1, D3.1 (K), D4.1 (K), J2.1, J3.1, Q11.5 (D), Q11.6 (D), Q11.7 (D), Q11.8 (D), R34.1
/V_SONDE: C22.1, J8.2, R39.2, U8.1 (I/O1), U8.6 (I/O1)
GND: BT1.2 (-), C1.2, C2.2, C3.2, C4.2, C5.2, C6.2, C7.2, C8.2, C9.2, C10.2, C11.2, C13.2, C14.2, C15.2, C16.2, C17.2, C18.2, C19.2, C20.2, C21.2, C22.2, C23.2, D2.2 (A), D9.1 (K), J1.2, J7.A1 (GND), J7.A12 (GND), J7.B1 (GND), J7.B12 (GND), J7.S1 (SHIELD), J8.1, J9.3, J9.6, J10.2, J11.2, J12.2, Q2.2 (S), Q3.2 (S), Q4.2 (S), Q5.2 (S), Q6.2 (S), Q10.2 (S), R1.2, R3.2, R5.2, R7.2, R9.2, R11.2, R15.2, R16.2, R25.2, R29.2, R31.2, R34.2, R36.2, R38.2, SW1.2, SW2.2, U1.1 (GND), U1.15 (GND), U1.38 (GND), U1.39 (GND/pastille), U2.2 (GND), U3.1 (GND), U4.5 (GND), U4.6 (GND), U4.7 (GND), U4.8 (GND), U4.9 (GND), U4.10 (GND), U4.11 (GND), U4.12 (GND), U4.13 (GND), U5.1 (GND), U6.2 (GND), U7.1 (GND), U8.2 (GND)

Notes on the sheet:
ENTREE 12 V : fusible, anti-inversion, ecreteur
Le DRAIN du transistor est cote fusible : sa diode interne laisse passer le courant dans le sens normal (note TI SLVA139). Le v2 etait monte a l'inverse. Ecreteur : au repos jusqu'a 13 V, limite a 21,5 V.
SORTIES 12 V : 2 pompes, filtration, eclairage, auxiliaire
Pompe pH
Pompe chlore
Filtration
Eclairage
Auxiliaire
Borne 1 = + de la charge, borne 2 = - commute. Diode de roue libre et 10 uF au pied de chaque sortie. POMPES : leur + vient de V_POMPES, coupe par l'interrupteur commun (cadre SECURITE DES POMPES). La diode de roue libre reste aux bornes de la pompe. Borniers debrochables : 5,08 mm pour filtration,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
ESP32 (module WROVER-E, 8 Mo flash, 8 Mo PSRAM)
IO12 : rien ne doit la tirer vers le haut au demarrage (tension de la memoire). IO16 et IO17 n'existent pas sur ce module (prises par la PSRAM). Memes broches que le v2 (ADR-0012) : le firmware ne change pas.
USB-C : programmation et remise a zero automatique
Le pont USB est alimente en 3,3 V : le 5 V de l'USB n'alimente rien. Les emetteurs des deux transistors sont croises (DTR/RTS). Boutons RESET et BOOT comme sur une carte de developpement. 470 Ohm en sortie du pont : un adaptateur serie branche sur J_DEBUG garde la main.
HORLOGE DS3231 et pile
Pile reliee directement a VBAT : la puce bascule seule et empeche la charge de la pile (fiche p. 9). 10 kOhm sur SDA et SCL : l'horloge repond meme carte de mesure debranchee.
TEMPERATURE, BOUTON, VOYANT
Bouton : appuye = niveau HAUT (c'est ce que lit le firmware).
LIAISON VERS LA CARTE DE MESURE (cable droit)
Meme ordre que le J1 de la carte de mesure. Voies 1 et 7 reunies (SDA), 2 et 8 reunies (SCL) : decision D3, un seul bus pour l'ESP32. Convertisseur du pH en 0x48, de l'ORP en 0x49, horloge en 0x51.
DETECTEUR DE DEBIT (contact sec, 2 fils)
Detecteur a palette (type electrolyseur) : un contact qui se ferme quand l'eau circule. Contact ferme = niveau BAS sur IO34 = debit present. Fil coupe ou detecteur absent = niveau HAUT = pas de debit : le doute va au refus. Rappel de 1 kOhm : une fuite d'eau entre les fils ne passe pas pour un debi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
CONNECTEUR DE DEBOGAGE (embase 2 x 8 avec detrompeur)
9 a 12 : sonde de debogage pas a pas (IO13 TCK, IO14 TMS, IO12 TDI, IO15 TDO). 13 : armement des pompes (IO4). 14 et 16 : relecture des pompes pH et chlore (IO18, IO23). 15 : non reliee. ⛔ Ne rien brancher sur 13, 14, 16 quand l'appareil dose. Soudee en usine sur cette version ; a retirer de la ver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
ALIMENTATIONS 5 V et 3,3 V
Cavalier JP1 : capuchon en place = fonctionnement normal sur le 12 V. Pour alimenter la logique et la mesure par le bornier 5 V externe : RETIRER le capuchon d'abord, et debrancher le 12 V pour un essai de bruit. Le transistor protege d'un 5 V externe branche a l'envers. Regulateur 5 V lineaire : 1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
SECURITE DES POMPES : coupure commune du 12 V et relecture
DEUX interrupteurs en serie par pompe : celui du haut (commun) et celui du bas (un par pompe). Si l'un tombe en panne passant, l'autre coupe, et la relecture le montre : - rail coupe, pompes non commandees : les deux relectures doivent lire 0 (sinon : interrupteur du haut en panne) ; - rail arme, p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
Sonde de temperature : 100 Ohm en serie sur son alimentation et sur son fil de donnees, et une protection contre les decharges au ras du bornier.

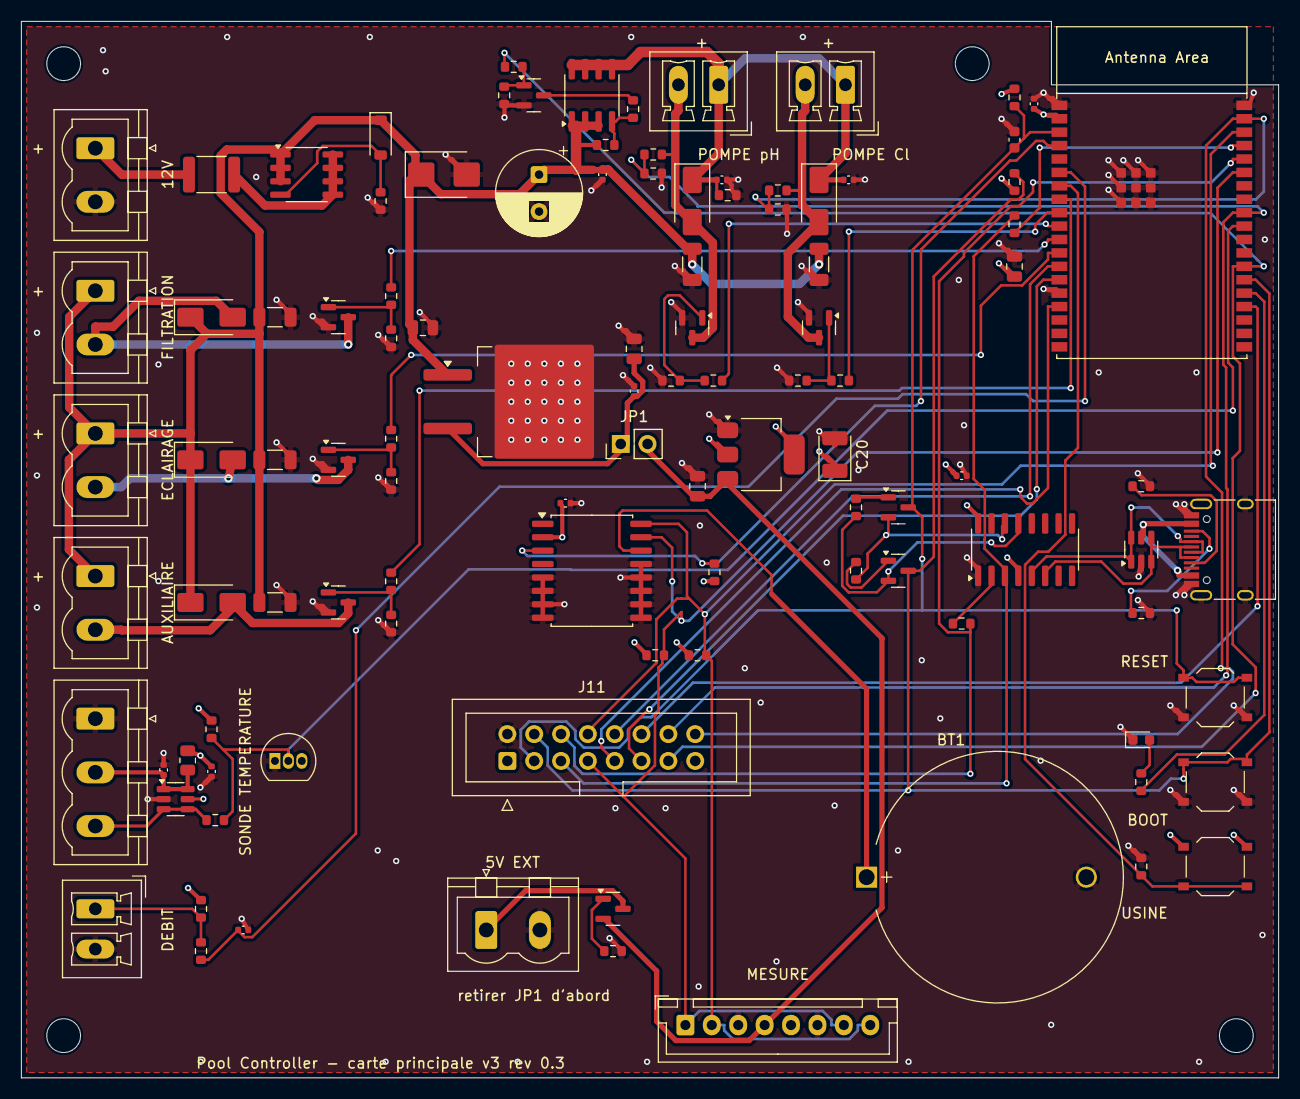
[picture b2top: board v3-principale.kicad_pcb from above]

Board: 4 copper layers, 119.0 x 100.0 mm, 110 parts (0 on the bottom side), 63 nets.

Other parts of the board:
H1, H2, H3, H4: Trou_M3_NPTH
